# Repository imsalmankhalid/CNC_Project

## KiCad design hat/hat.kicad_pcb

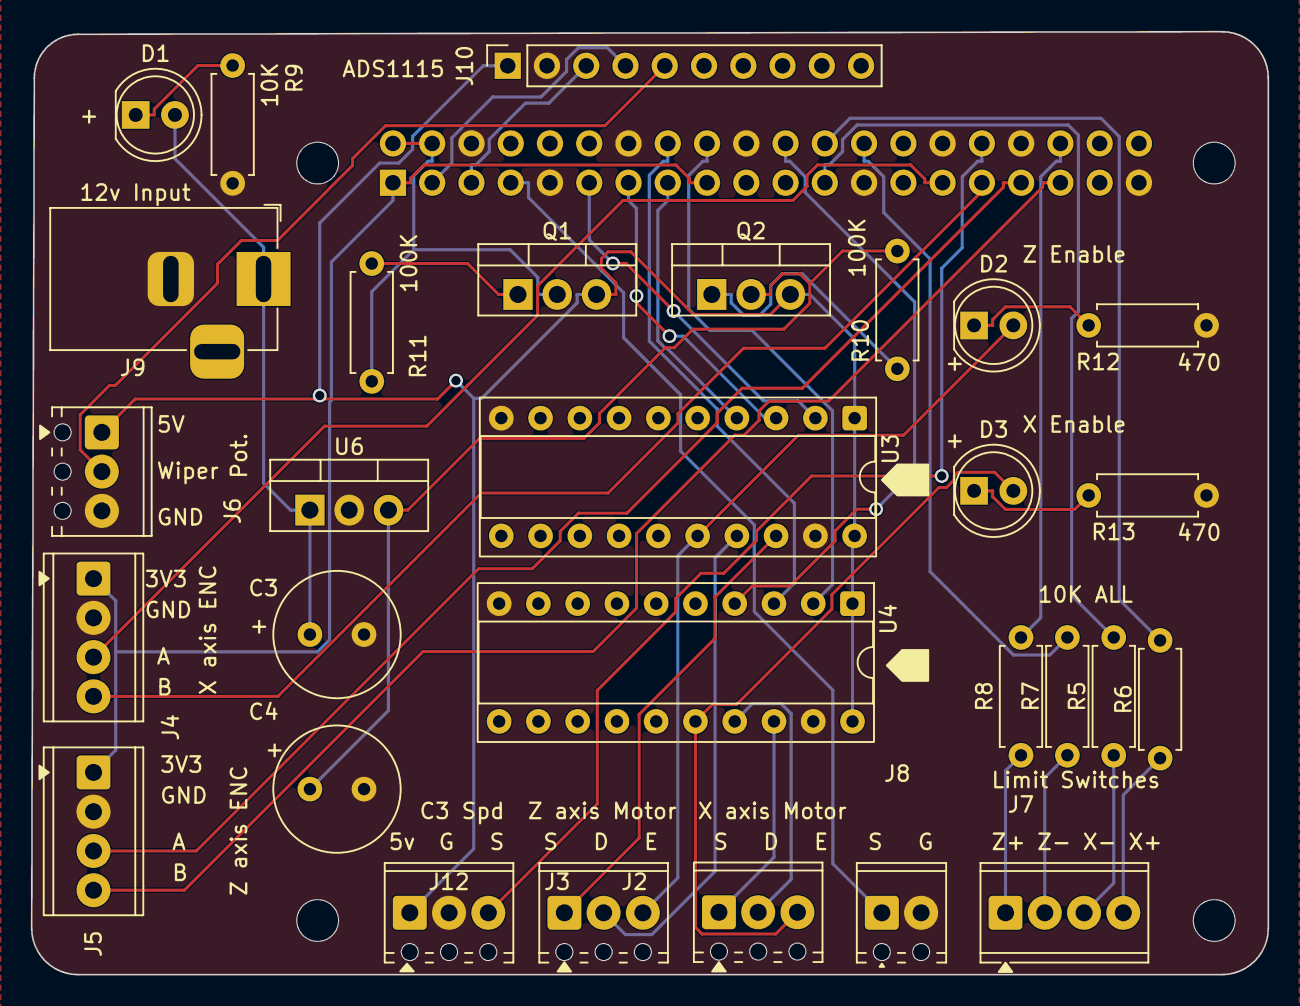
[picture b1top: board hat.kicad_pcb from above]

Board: 2 copper layers, 80.0 x 61.0 mm, 34 parts (1 on the bottom side), 40 nets.

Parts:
C3: 100uF 50v; C_Radial_D8.0mm_H11.5mm_P3.50mm
C4: 10uF 25v; C_Radial_D8.0mm_H11.5mm_P3.50mm
D1, D2, D3: LED; LED_D5.0mm
J1: GPIO; PinSocket_2x20_P2.54mm_Vertical
J2: x axis motor; TerminalBlock_Phoenix_MPT-0,5-3-2.54_1x03_P2.54mm_Horizontal
J3: Z axis motor; TerminalBlock_Phoenix_MPT-0,5-3-2.54_1x03_P2.54mm_Horizontal
J4: x axis enc; TerminalBlock_Phoenix_MPT-0,5-4-2.54_1x04_P2.54mm_Horizontal
J5: z axis enc; TerminalBlock_Phoenix_MPT-0,5-4-2.54_1x04_P2.54mm_Horizontal
J6: Pot; TerminalBlock_Phoenix_MPT-0,5-3-2.54_1x03_P2.54mm_Horizontal
J7: Limit switches; TerminalBlock_Phoenix_MPT-0,5-4-2.54_1x04_P2.54mm_Horizontal
J8: Screw_Terminal_01x02; TerminalBlock_Phoenix_MPT-0,5-2-2.54_1x02_P2.54mm_Horizontal
J9: Barrel_Jack_Switch; BarrelJack_Horizontal
J10: Conn_01x10; PinSocket_1x10_P2.54mm_Vertical
J12: Speed sensor; TerminalBlock_Phoenix_MPT-0,5-3-2.54_1x03_P2.54mm_Horizontal
MH1, MH2, MH3, MH4: MountingHole_2.7mm_M2.5
Q1, Q2: IRF4905; TO-220-3_Vertical
R5, R6, R7, R8, R9: 10k; R_Axial_DIN0207_L6.3mm_D2.5mm_P7.62mm_Horizontal
R10, R11: 100k; R_Axial_DIN0207_L6.3mm_D2.5mm_P7.62mm_Horizontal
R12, R13: 470; R_Axial_DIN0207_L6.3mm_D2.5mm_P7.62mm_Horizontal
U3, U4: 74HC245; DIP-20_W7.62mm_Socket
U6: L7805; TO-220-3_Vertical

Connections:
+3V3: J1.1, J1.17, J4.1, J5.1
+5V: J6.1, J10.1, J12.1, Q1.3 (S), Q2.3 (S), U3.1 (A->B), U3.20 (VCC), U4.1 (A->B), U4.20 (VCC)
/GPIO2/SDA1: J1.3, J10.4
/GPIO3/SCL1: J1.5, J10.3
/GPIO4/GPCLK0: J1.7, J8.1
/GPIO5: J1.29, J4.3
/GPIO6: J1.31, J4.4
/GPIO7/SPI0.CE1: J1.26, R7.2
/GPIO8/SPI0.CE0: J1.24, R6.2
/GPIO11/SPI0.SCLK: J1.23, R5.2
/GPIO12/PWM0: J1.32, J12.3
/GPIO13/PWM1: J1.33, J5.3
/GPIO16: J1.36, R8.2
/GPIO17: J1.11, U3.2 (A0)
/GPIO19/PCM.FS: J1.35, J5.4
/GPIO22: J1.15, U3.4 (A2)
/GPIO23: J1.16, U4.3 (A1)
/GPIO24: J1.18, U4.2 (A0)
/GPIO25: J1.22, U4.4 (A2)
/GPIO27: J1.13, U3.3 (A1)
/POT: J6.2, J10.5
GND: C3.2, C4.2, J1.6, J1.9, J1.14, J1.20, J1.25, J1.30, J1.34, J1.39, J4.2, J5.2, J6.3, J8.2, J9.2, J10.2, J12.2, R9.1, R12.1, R13.1, U3.10 (GND), U3.19 (CE), U4.10 (GND), U4.19 (CE), U6.2 (GND)
unnamed: C3.1, D1.2 (A), J9.1, U6.1 (IN)
unnamed: D1.1 (K), R9.2
unnamed: D2.2 (A), J3.3, U3.16 (B2)
unnamed: D2.1 (K), R12.2
unnamed: D3.2 (A), J2.3, U4.16 (B2)
unnamed: D3.1 (K), R13.2
unnamed: J1.2, J1.4, Q1.2 (D), R11.2
unnamed: J2.1, U4.18 (B0)
unnamed: J2.2, U4.17 (B1)
unnamed: J3.1, U3.18 (B0)
unnamed: J3.2, U3.17 (B1)
unnamed: J7.1, R8.1
unnamed: J7.2, R7.1
unnamed: J7.3, R5.1
unnamed: J7.4, R6.1
unnamed: Q1.1 (G), R11.1
unnamed: C4.1, Q2.2 (D), R10.2, U6.3 (OUT)
unnamed: Q2.1 (G), R10.1
